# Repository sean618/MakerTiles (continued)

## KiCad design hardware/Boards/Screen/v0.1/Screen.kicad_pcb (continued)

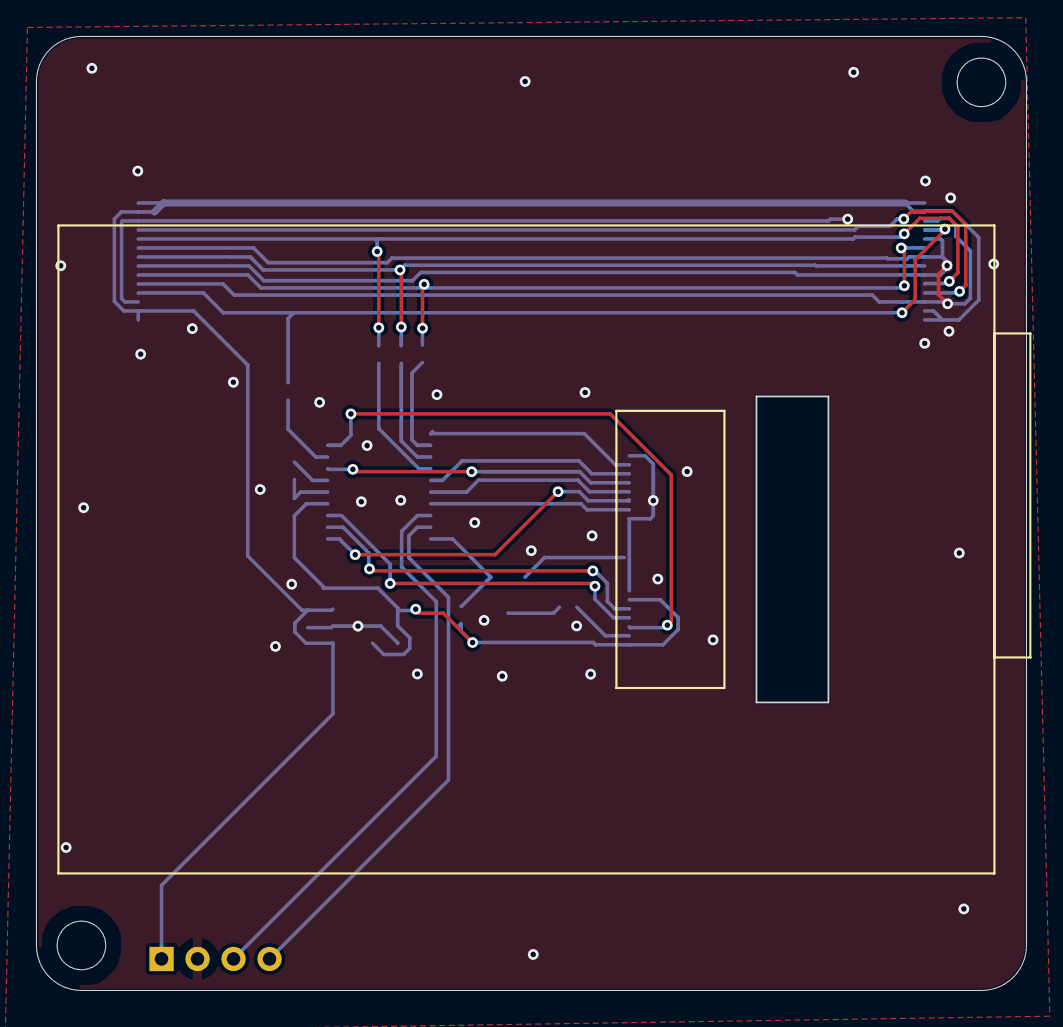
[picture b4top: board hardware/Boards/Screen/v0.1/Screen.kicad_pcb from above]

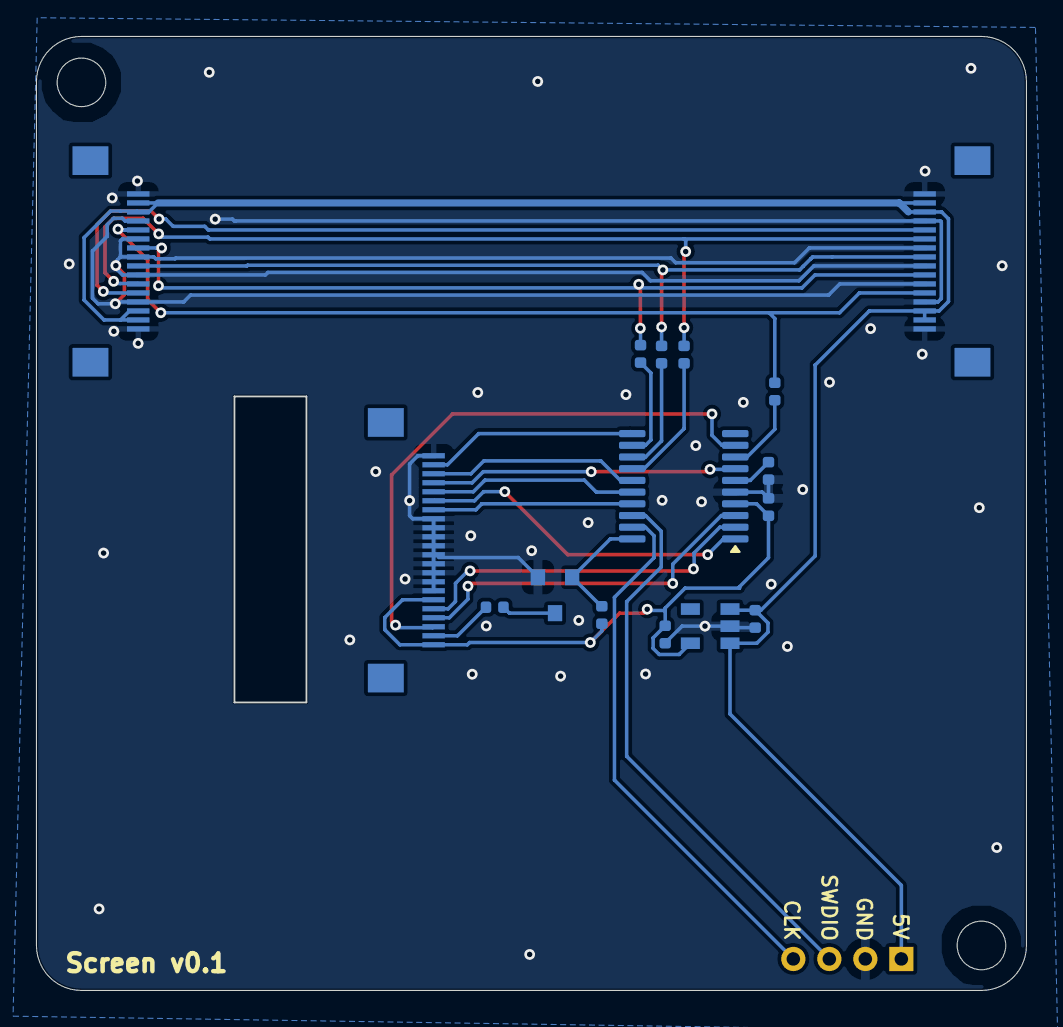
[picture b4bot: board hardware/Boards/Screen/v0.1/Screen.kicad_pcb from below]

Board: 2 copper layers, 55.0 x 53.0 mm, 21 parts (16 on the bottom side), 27 nets.

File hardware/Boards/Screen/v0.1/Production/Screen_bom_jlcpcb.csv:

Comment,Designator,Footprint,LCSC Part Number
4.7uF,"C9,C8,C2",C_0402_1005Metric,C23733
FFC_connector_16p_hinge_lock,"J1,J2",FFC_connector_16p_hinge_lock,C262665
FFC_connector_22p_dual_sided,J3,FFC_connector_22p_hinge_lock,C557729
ME6211C33M5G-N,U2,SOT-23-5,C81233
75R,"R2,R3,R4,R1",R_0402_1005Metric,C25133
STM32G030F6P6,U3,TSSOP-20_4.4x6.5mm_P0.65mm,C529330
N_MOSFET,Q2,SOT-23,C8545
0.1uF,C1,C_0402_1005Metric,C1525
10R,R5,R_0402_1005Metric,C25077
10K,R7,R_0402_1005Metric,C25744

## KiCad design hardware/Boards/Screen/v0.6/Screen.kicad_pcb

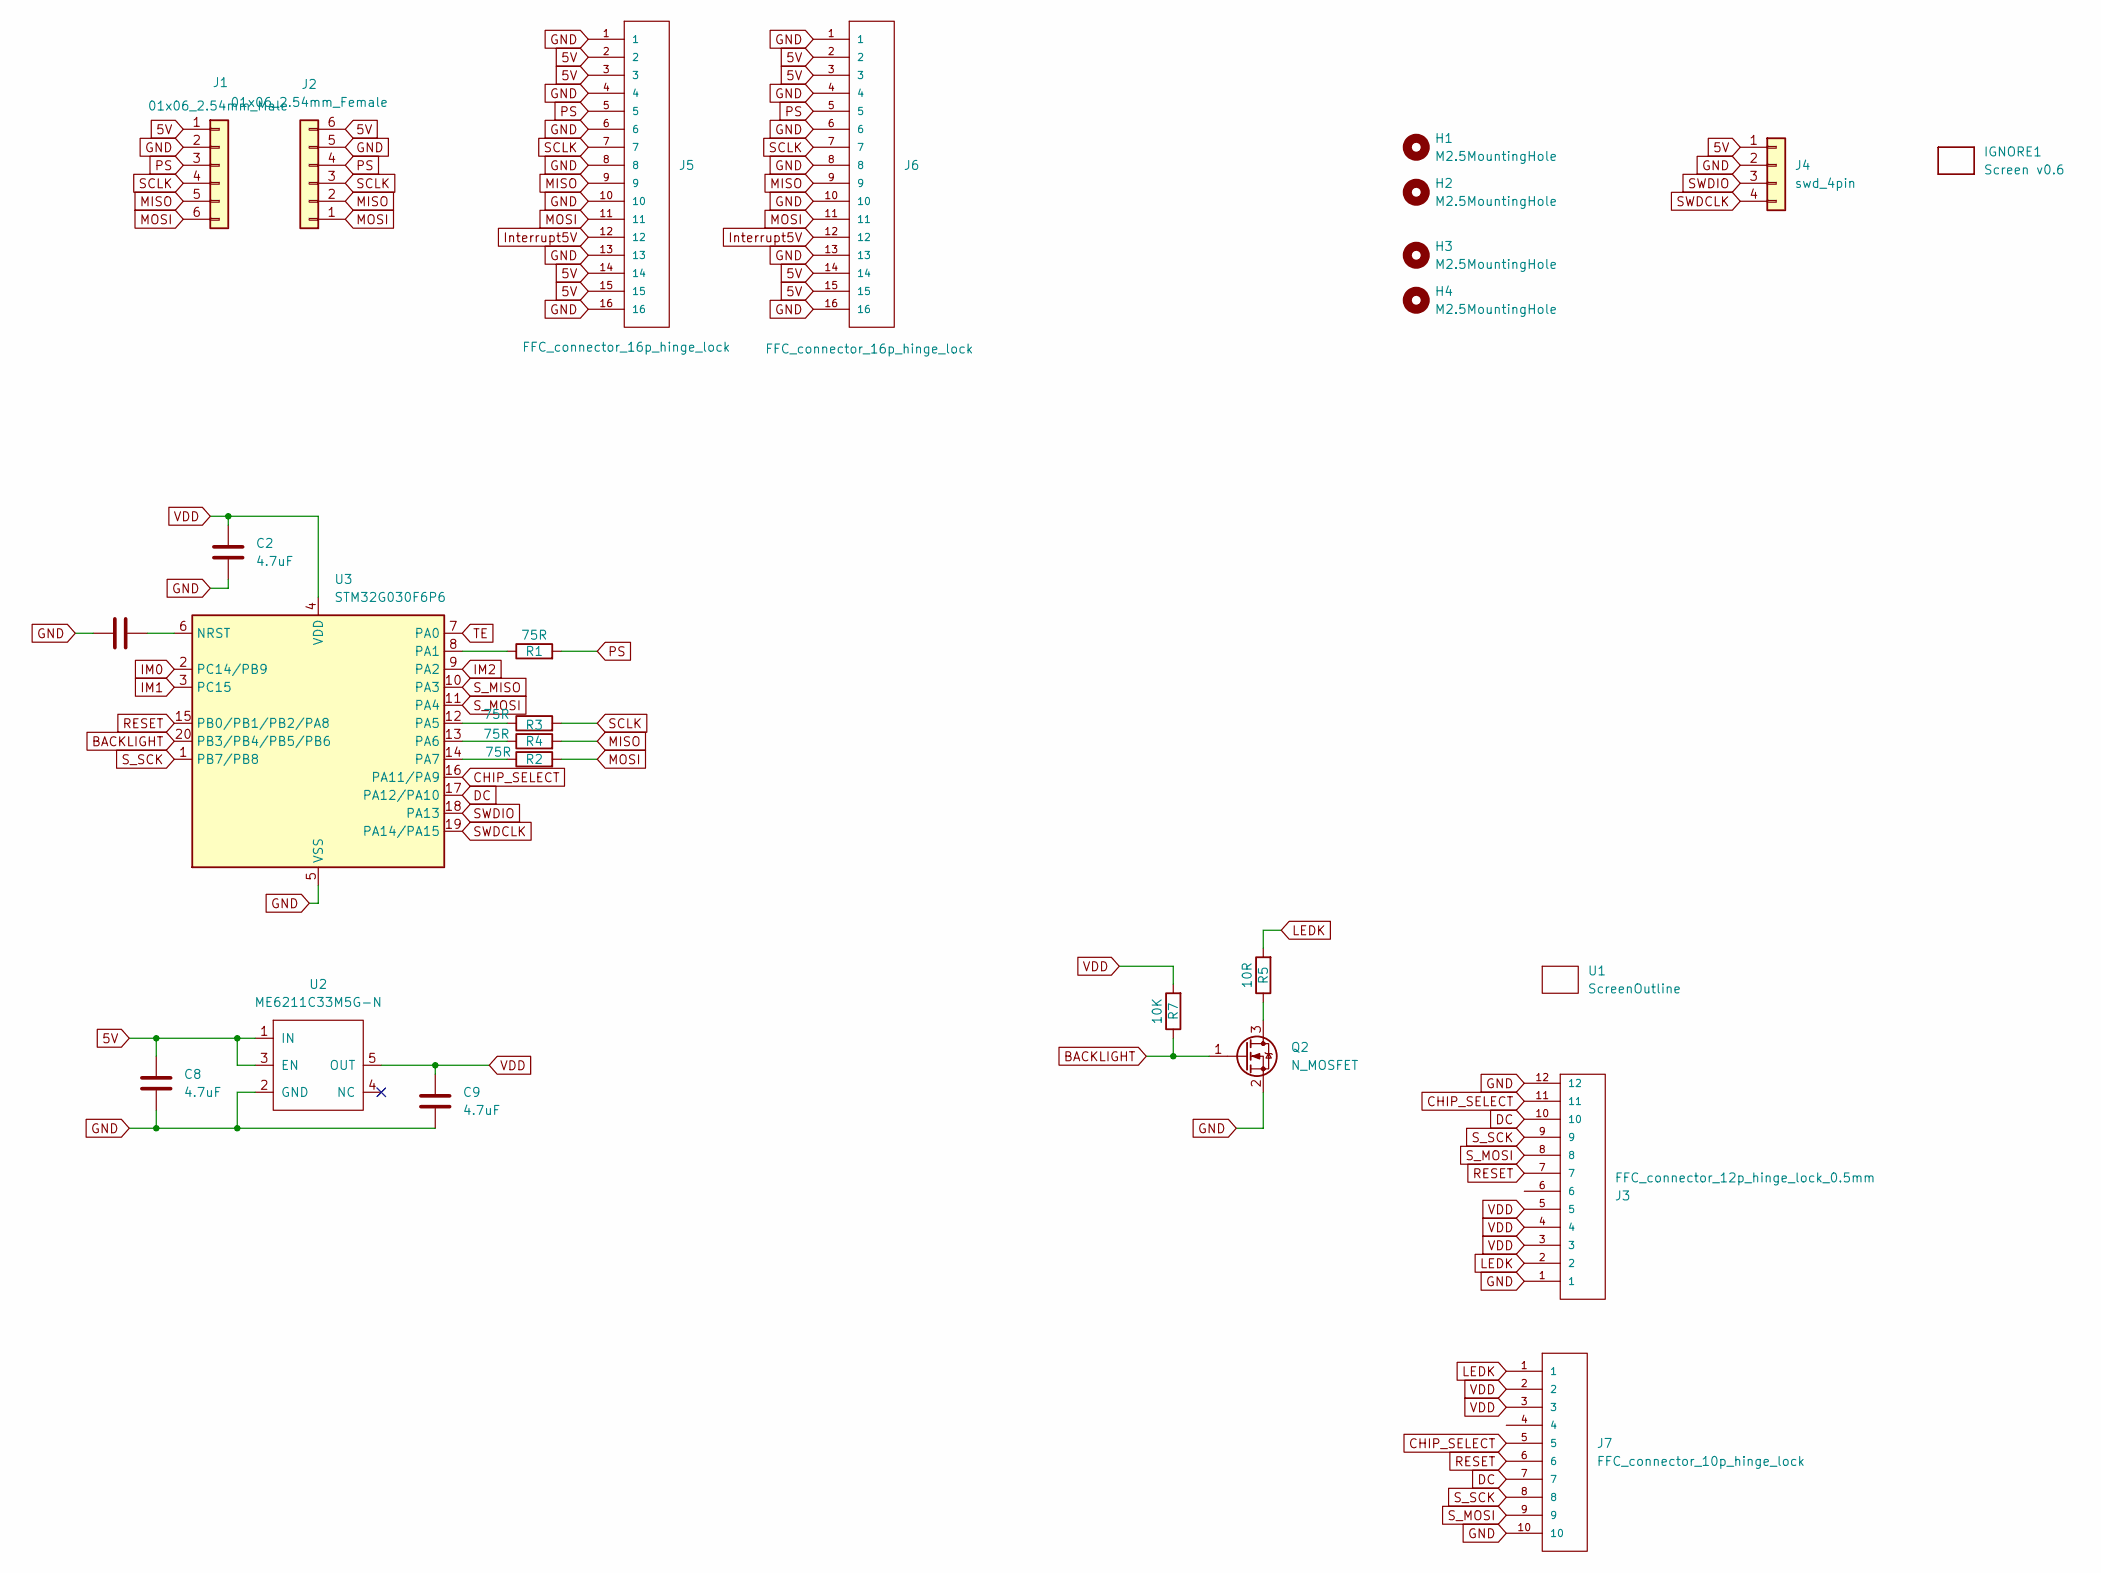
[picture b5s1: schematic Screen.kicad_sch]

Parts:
C1: 0.1uF; C_0402_1005Metric
C2, C8, C9: 4.7uF; C_0402_1005Metric
H1, H2, H3, H4: M2.5MountingHole; MountingHole_2.7mm_M2.5_ISO7380
IGNORE1: Screen v0.6; BoardText
J1: 01x06_2.54mm_Male
J2: 01x06_2.54mm_Female
J3: FFC_connector_12p_hinge_lock_0.5mm
J4: swd_4pin; swd_header
J5, J6: FFC_connector_16p_hinge_lock
J7: FFC_connector_10p_hinge_lock
Q2: N_MOSFET; SOT-23
R1, R2, R3, R4: 75R; R_0402_1005Metric
R5: 10R; R_0402_1005Metric
R7: 10K; R_0402_1005Metric
U1: ScreenOutline; 2InchScreen
U2: ME6211C33M5G-N; SOT-23-5
U3: STM32G030F6P6; TSSOP-20_4.4x6.5mm_P0.65mm

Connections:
5V: C8.1, J1.1, J2.6, J4.1, J5.2, J5.3, J5.14, J5.15, J6.2, J6.3, J6.14, J6.15, U2.1 (IN), U2.3 (EN)
BACKLIGHT: Q2.1 (G), R7.1, U3.20 (PB3/PB4/PB5/PB6)
CHIP_SELECT: J3.11, J7.5, U3.16 (PA11/PA9)
DC: J3.10, J7.7, U3.17 (PA12/PA10)
GND: C1.2, C2.2, C8.2, C9.2, J1.2, J2.5, J3.1, J3.12, J4.2, J5.1, J5.4, J5.6, J5.8, J5.10, J5.13, J5.16, J6.1, J6.4, J6.6, J6.8, J6.10, J6.13, J6.16, J7.10, Q2.2 (S), U2.2 (GND), U3.5 (VSS)
IM0: U3.2 (PC14/PB9)
IM1: U3.3 (PC15)
IM2: U3.9 (PA2)
Interrupt5V: J5.12, J6.12
LEDK: J3.2, J7.1, R5.2
MISO: J1.5, J2.2, J5.9, J6.9, R4.2
MOSI: J1.6, J2.1, J5.11, J6.11, R2.2
unnamed: Q2.3 (D), R5.1
unnamed: C1.1, U3.6 (NRST)
unnamed: R1.1, U3.8 (PA1)
unnamed: R3.1, U3.12 (PA5)
unnamed: R4.1, U3.13 (PA6)
unnamed: R2.1, U3.14 (PA7)
PS: J1.3, J2.4, J5.5, J6.5, R1.2
RESET: J3.7, J7.6, U3.15 (PB0/PB1/PB2/PA8)
SCLK: J1.4, J2.3, J5.7, J6.7, R3.2
SWDCLK: J4.4, U3.19 (PA14/PA15)
SWDIO: J4.3, U3.18 (PA13)
S_MISO: U3.10 (PA3)
S_MOSI: J3.8, J7.9, U3.11 (PA4)
S_SCK: J3.9, J7.8, U3.1 (PB7/PB8)
TE: U3.7 (PA0)
VDD: C2.1, C9.1, J3.3, J3.4, J3.5, J7.2, J7.3, R7.2, U2.5 (OUT), U3.4 (VDD)

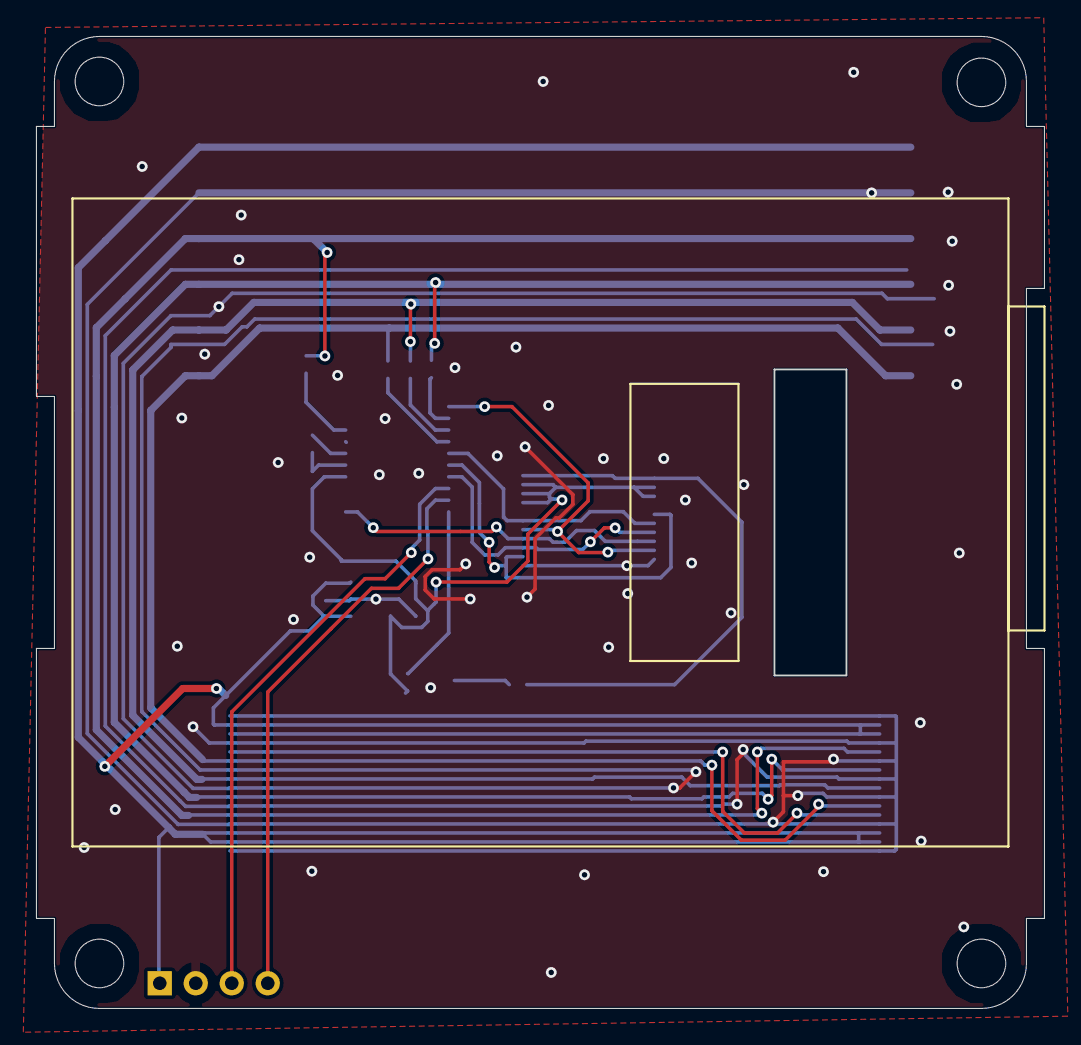
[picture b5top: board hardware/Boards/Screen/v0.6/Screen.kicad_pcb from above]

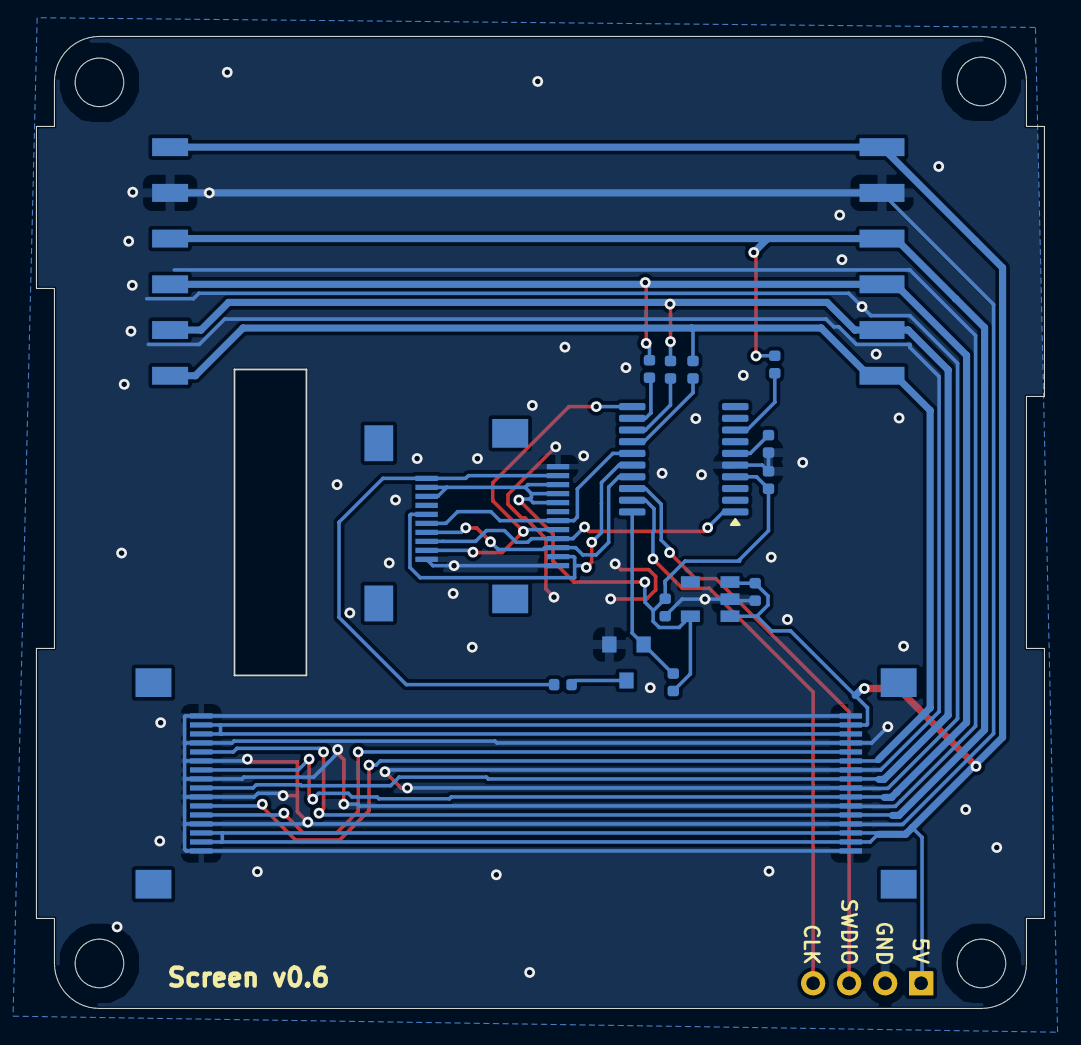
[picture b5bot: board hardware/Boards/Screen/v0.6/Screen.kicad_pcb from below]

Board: 2 copper layers, 56.0 x 54.0 mm, 26 parts (19 on the bottom side), 23 nets.

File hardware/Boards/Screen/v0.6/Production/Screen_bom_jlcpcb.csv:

Comment,Designator,Footprint,LCSC Part Number
4.7uF,"C9,C8,C2",C_0402_1005Metric,C23733
FFC_connector_12p_hinge_lock_0.5mm,J3,FFC_connector_12p_hinge_lock_0.5mm,C262661
FFC_connector_16p_hinge_lock,"J5,J6",FFC_connector_16p_hinge_lock,C262665
ME6211C33M5G-N,U2,SOT-23-5,C81233
75R,"R2,R3,R4,R1",R_0402_1005Metric,C25133
STM32G030F6P6,U3,TSSOP-20_4.4x6.5mm_P0.65mm,C529330
N_MOSFET,Q2,SOT-23,C8545
0.1uF,C1,C_0402_1005Metric,C1525
FFC_connector_10p_hinge_lock,J7,FFC_connector_10p_hinge_lock,C262659
01x06_2.54mm_Female,J2,01x06_2.54mm_Female,C5142239
10R,R5,R_0402_1005Metric,C25077
01x06_2.54mm_Male,J1,01x06_2.54mm_Male,C5242199
10K,R7,R_0402_1005Metric,C25744

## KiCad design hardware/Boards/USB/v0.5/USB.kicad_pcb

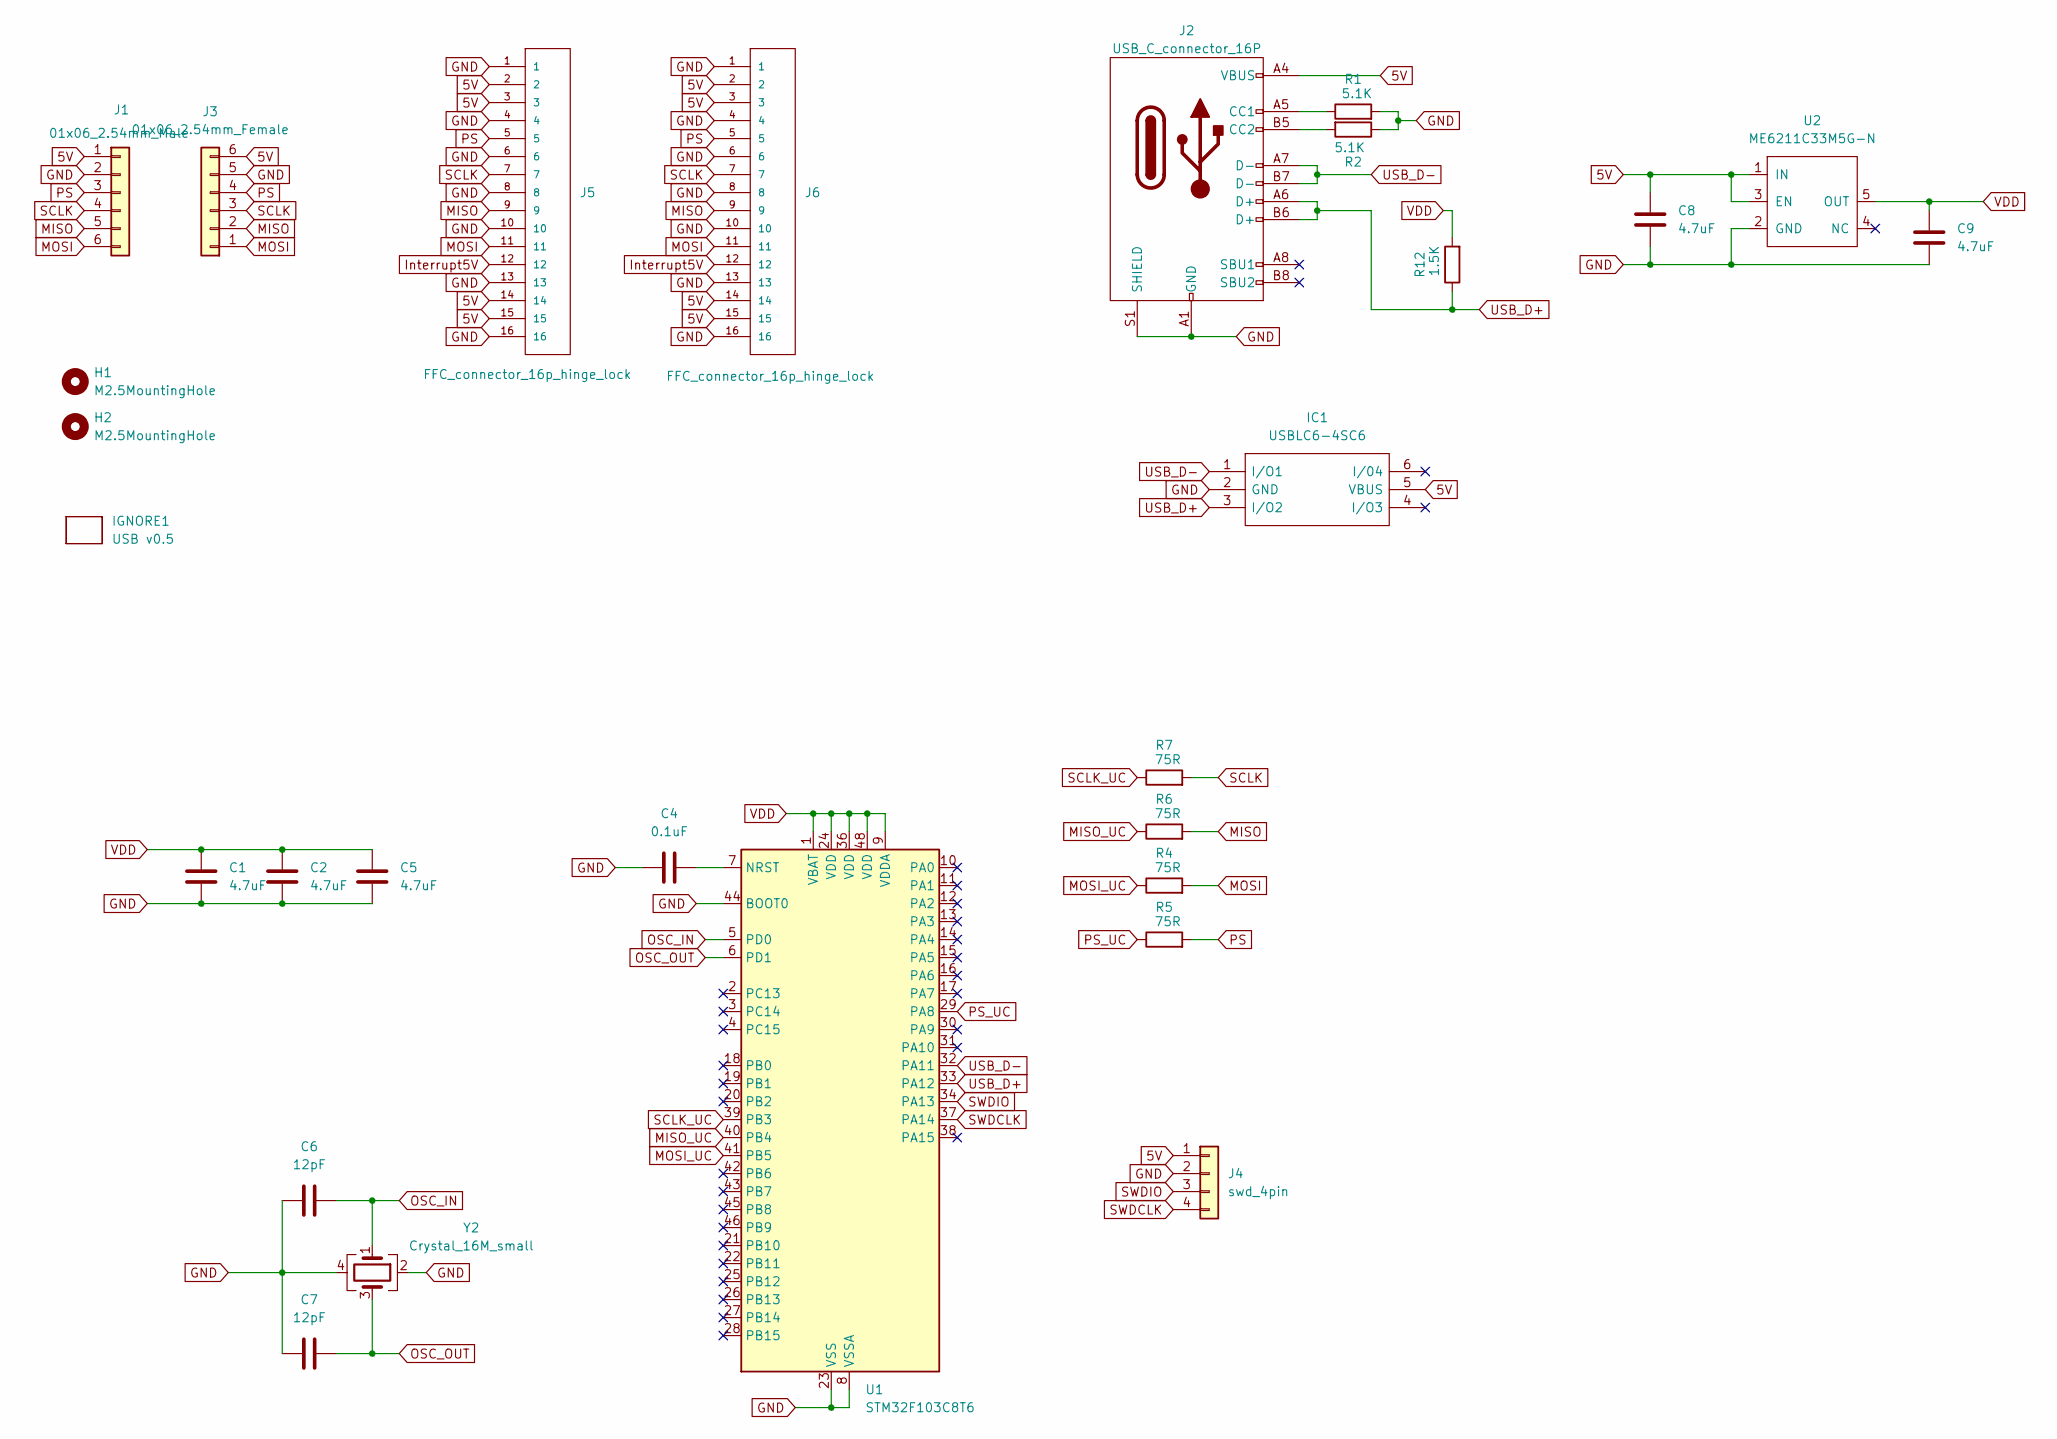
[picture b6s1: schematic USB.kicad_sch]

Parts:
C1, C2, C5, C8, C9: 4.7uF; C_0402_1005Metric
C4: 0.1uF; C_0402_1005Metric
C6, C7: 12pF; C_0402_1005Metric
H1, H2: M2.5MountingHole; MountingHole_2.7mm_M2.5_ISO7380
IC1: USBLC6-4SC6; SOT-23-6; Manufacturer_Part_Number USBLC6-2P6
IGNORE1: USB v0.5; BoardText
J1: 01x06_2.54mm_Male
J2: USB_C_connector_16P; USB_C_Receptacle_16P
J3: 01x06_2.54mm_Female
J4: swd_4pin; swd_header
J5, J6: FFC_connector_16p_hinge_lock
R1, R2: 5.1K; R_0402_1005Metric
R4, R5, R6, R7: 75R; R_0402_1005Metric
R12: 1.5K; R_0402_1005Metric
U1: STM32F103C8T6; LQFP-48_7x7mm_P0.5mm
U2: ME6211C33M5G-N; SOT-23-5
Y2: Crystal_16M_small; Crystal_SMD_2016-4Pin_2.0x1.6mm

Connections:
5V: C8.1, IC1.5 (VBUS), J1.1, J2.A4 (VBUS), J2.A9 (VBUS), J2.B4 (VBUS), J2.B9 (VBUS), J3.6, J4.1, J5.2, J5.3, J5.14, J5.15, J6.2, J6.3, J6.14, J6.15, U2.1 (IN), U2.3 (EN)
GND: C1.2, C2.2, C4.1, C5.2, C6.1, C7.1, C8.2, C9.2, IC1.2 (GND), J1.2, J2.A1 (GND), J2.A12 (GND), J2.B1 (GND), J2.B12 (GND), J2.S1 (SHIELD), J3.5, J4.2, J5.1, J5.4, J5.6, J5.8, J5.10, J5.13, J5.16, J6.1, J6.4, J6.6, J6.8, J6.10, J6.13, J6.16, R1.2, R2.1, U1.8 (VSSA), U1.23 (VSS), U1.35 (VSS), U1.44 (BOOT0), U1.47 (VSS), U2.2 (GND), Y2.2 (GND), Y2.4 (GND)
Interrupt5V: J5.12, J6.12
MISO: J1.5, J3.2, J5.9, J6.9, R6.2
MISO_UC: R6.1, U1.40 (PB4)
MOSI: J1.6, J3.1, J5.11, J6.11, R4.2
MOSI_UC: R4.1, U1.41 (PB5)
unnamed: J2.A5 (CC1), R1.1
unnamed: J2.B5 (CC2), R2.2
unnamed: C4.2, U1.7 (NRST)
OSC_IN: C6.2, U1.5 (PD0), Y2.1
OSC_OUT: C7.2, U1.6 (PD1), Y2.3
PS: J1.3, J3.4, J5.5, J6.5, R5.2
PS_UC: R5.1, U1.29 (PA8)
SCLK: J1.4, J3.3, J5.7, J6.7, R7.2
SCLK_UC: R7.1, U1.39 (PB3)
SWDCLK: J4.4, U1.37 (PA14)
SWDIO: J4.3, U1.34 (PA13)
USB_D+: IC1.3 (I/O2), J2.A6 (D+), J2.B6 (D+), R12.1, U1.33 (PA12)
USB_D-: IC1.1 (I/O1), J2.A7 (D-), J2.B7 (D-), U1.32 (PA11)
VDD: C1.1, C2.1, C5.1, C9.1, R12.2, U1.1 (VBAT), U1.9 (VDDA), U1.24 (VDD), U1.36 (VDD), U1.48 (VDD), U2.5 (OUT)

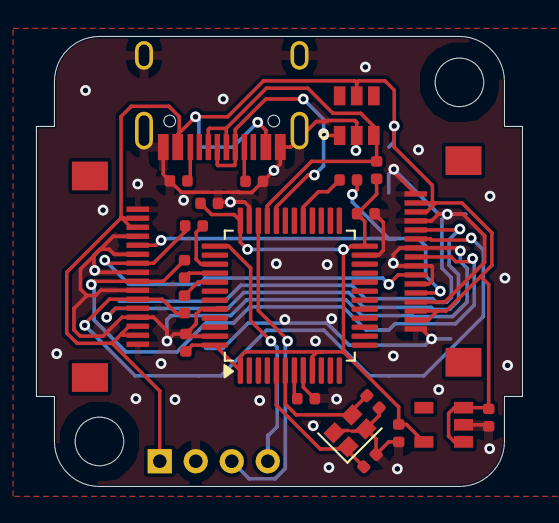
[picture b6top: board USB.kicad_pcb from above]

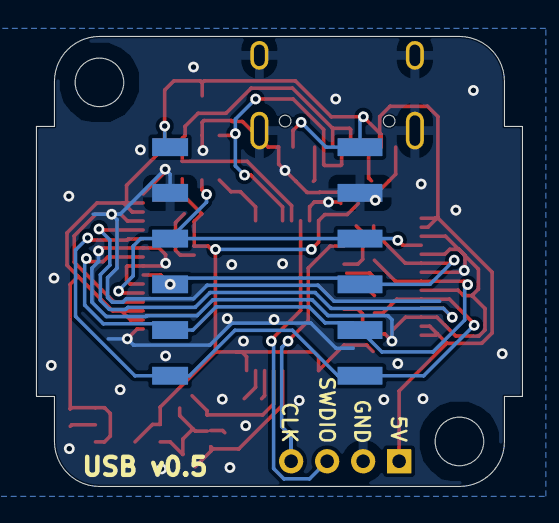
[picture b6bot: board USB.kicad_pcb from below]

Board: 4 copper layers, 27.0 x 25.0 mm, 28 parts (2 on the bottom side), 21 nets.

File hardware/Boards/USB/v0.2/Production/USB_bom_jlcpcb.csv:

Comment,Designator,Footprint,LCSC Part Number
1.5K,R12,R_0402_1005Metric,C25867
4.7uF,"C9,C2,C8,C3,C5,C1",C_0402_1005Metric,C23733
FFC_connector_16p_hinge_lock,"J1,J3",FFC_connector_16p_hinge_lock,C262665
12pF,"C6,C7",C_0402_1005Metric,C1547
STM32F103C8T6,U1,LQFP-48_7x7mm_P0.5mm,C2969777
100R,"R7,R4,R5,R6",R_0402_1005Metric,C25076
ME6211C33M5G-N,U2,SOT-23-5,C82942
5.1K,"R2,R1",R_0402_1005Metric,C25905
USBLC6-4SC6,IC1,SOT-23-6,C558419
0.1uF,C4,C_0402_1005Metric,C1525
Crystal_16M,Y1,Crystal_SMD_3225-4Pin_3.2x2.5mm,C13738
USB_C_connector_16P,J2,USB_C_Receptacle_16P,C319148

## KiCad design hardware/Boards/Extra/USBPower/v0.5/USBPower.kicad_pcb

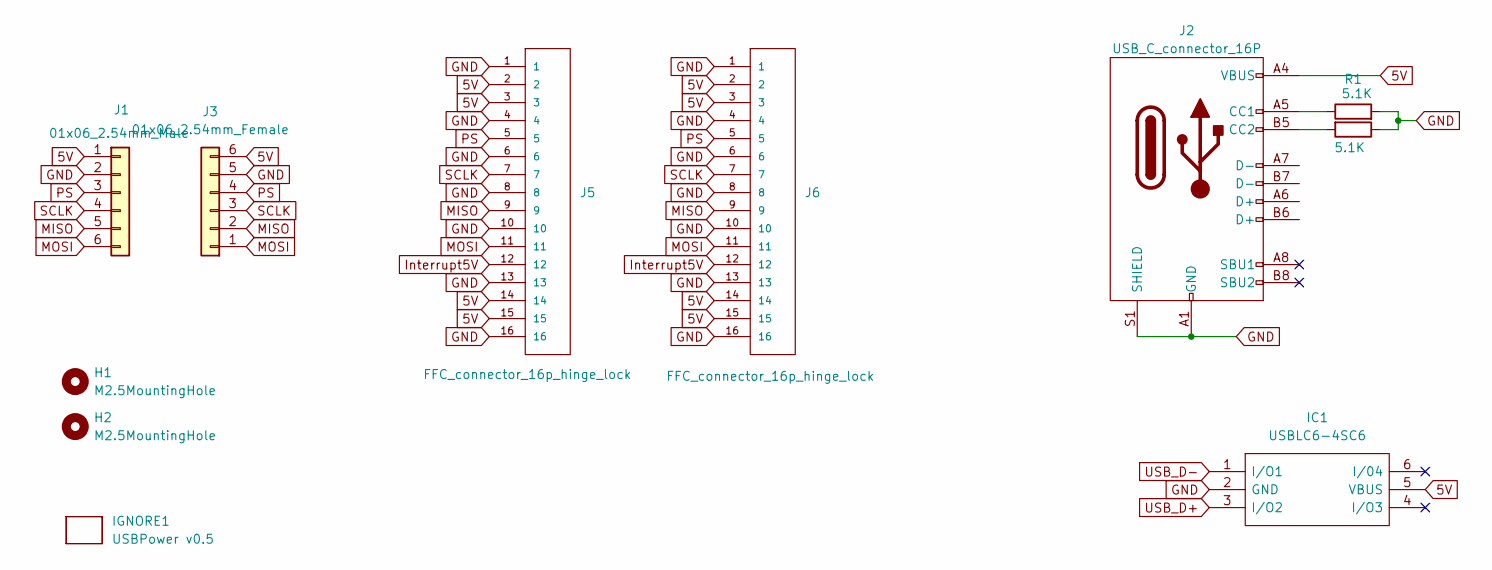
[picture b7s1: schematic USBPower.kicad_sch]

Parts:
H1, H2: M2.5MountingHole; MountingHole_2.7mm_M2.5_ISO7380
IC1: USBLC6-4SC6; SOT-23-6; Manufacturer_Part_Number USBLC6-2P6
IGNORE1: USBPower v0.5; BoardText
J1: 01x06_2.54mm_Male
J2: USB_C_connector_16P; USB_C_Receptacle_16P
J3: 01x06_2.54mm_Female
J5, J6: FFC_connector_16p_hinge_lock
R1, R2: 5.1K; R_0402_1005Metric

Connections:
5V: IC1.5 (VBUS), J1.1, J2.A4 (VBUS), J2.A9 (VBUS), J2.B4 (VBUS), J2.B9 (VBUS), J3.6, J5.2, J5.3, J5.14, J5.15, J6.2, J6.3, J6.14, J6.15
GND: IC1.2 (GND), J1.2, J2.A1 (GND), J2.A12 (GND), J2.B1 (GND), J2.B12 (GND), J2.S1 (SHIELD), J3.5, J5.1, J5.4, J5.6, J5.8, J5.10, J5.13, J5.16, J6.1, J6.4, J6.6, J6.8, J6.10, J6.13, J6.16, R1.2, R2.1
Interrupt5V: J5.12, J6.12
MISO: J1.5, J3.2, J5.9, J6.9
MOSI: J1.6, J3.1, J5.11, J6.11
unnamed: J2.A5 (CC1), R1.1
unnamed: J2.B5 (CC2), R2.2
PS: J1.3, J3.4, J5.5, J6.5
SCLK: J1.4, J3.3, J5.7, J6.7
USB_D+: IC1.3 (I/O2)
USB_D-: IC1.1 (I/O1)

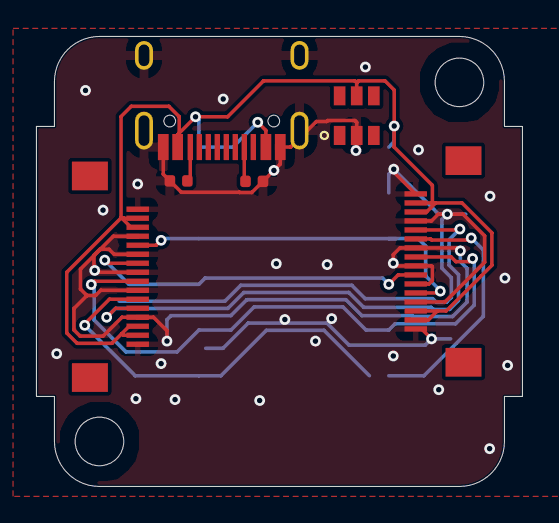
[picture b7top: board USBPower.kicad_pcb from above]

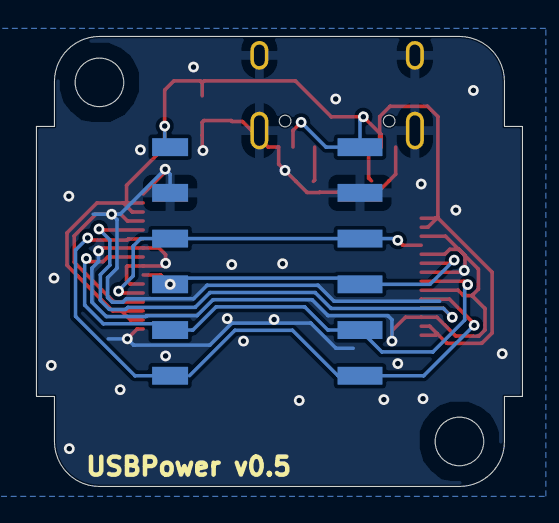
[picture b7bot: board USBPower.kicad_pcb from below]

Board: 4 copper layers, 27.0 x 25.0 mm, 11 parts (2 on the bottom side), 9 nets.

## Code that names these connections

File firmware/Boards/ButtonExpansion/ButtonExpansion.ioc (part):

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Mcu.Name=STM32G030K(6-8)Tx
Mcu.Package=LQFP32
Mcu.UserName=STM32G030K6Tx
PA0.Mode=Full_Duplex_Slave
PA0.Signal=SPI2_SCK
PA1.GPIOParameters=GPIO_PuPd
PA1.GPIO_PuPd=GPIO_NOPULL
PA1.Signal=GPXTI1
PA10.Mode=Full_Duplex_Slave
PA10.Signal=SPI2_MOSI
PA11\ [PA9].GPIOParameters=GPIO_PuPd
PA11\ [PA9].GPIO_PuPd=GPIO_PULLUP
PA11\ [PA9].Signal=GPIO_Input
PA12\ [PA10].GPIOParameters=GPIO_PuPd
PA12\ [PA10].GPIO_PuPd=GPIO_PULLUP
PA12\ [PA10].Signal=GPIO_Input
PA13.Mode=Serial_Wire
PA13.Signal=SYS_SWDIO
PA14-BOOT0.Mode=Serial_Wire
PA14-BOOT0.Signal=SYS_SWCLK
PA15.GPIOParameters=GPIO_PuPd
PA15.GPIO_PuPd=GPIO_PULLUP
PA15.Signal=GPIO_Input
PA2.GPIOParameters=GPIO_PuPd
PA2.GPIO_PuPd=GPIO_PULLUP
PA2.Signal=GPIO_Input
PA3.GPIOParameters=GPIO_PuPd
PA3.GPIO_PuPd=GPIO_PULLUP
PA3.Signal=GPIO_Input
PA4.GPIOParameters=GPIO_PuPd
PA4.GPIO_PuPd=GPIO_PULLUP
PA4.Signal=GPIO_Input
PA5.GPIOParameters=GPIO_PuPd
PA5.GPIO_PuPd=GPIO_PULLUP
PA5.Signal=GPIO_Input
PA6.GPIOParameters=GPIO_PuPd
PA6.GPIO_PuPd=GPIO_PULLUP
PA6.Signal=GPIO_Input
PA7.GPIOParameters=GPIO_PuPd
PA7.GPIO_PuPd=GPIO_PULLUP
PA7.Signal=GPIO_Input
PA8.GPIOParameters=GPIO_PuPd
PA8.GPIO_PuPd=GPIO_PULLUP
PA8.Signal=GPIO_Input
PA9.Mode=Full_Duplex_Slave
PA9.Signal=SPI2_MISO
PB0.GPIOParameters=GPIO_PuPd
PB0.GPIO_PuPd=GPIO_PULLUP
PB0.Signal=GPIO_Input
PB1.GPIOParameters=GPIO_PuPd
PB1.GPIO_PuPd=GPIO_PULLUP
PB1.Signal=GPIO_Input
PB2.GPIOParameters=GPIO_PuPd
PB2.GPIO_PuPd=GPIO_PULLUP
PB2.Signal=GPIO_Input
PB3.GPIOParameters=GPIO_PuPd
PB3.GPIO_PuPd=GPIO_PULLUP
PB3.Signal=GPIO_Input
PB4.GPIOParameters=GPIO_PuPd
PB4.GPIO_PuPd=GPIO_PULLUP
PB4.Signal=GPIO_Input
PB5.GPIOParameters=GPIO_PuPd
PB5.GPIO_PuPd=GPIO_PULLUP
PB5.Signal=GPIO_Input
PB6.GPIOParameters=GPIO_PuPd
PB6.GPIO_PuPd=GPIO_PULLUP
PB6.Signal=GPIO_Input
PB7.GPIOParameters=GPIO_PuPd
PB7.GPIO_PuPd=GPIO_PULLUP
PB7.Signal=GPIO_Input
PB8.GPIOParameters=GPIO_PuPd
PB8.GPIO_PuPd=GPIO_PULLUP
PB8.Signal=GPIO_Input
PB9.GPIOParameters=GPIO_PuPd
PB9.GPIO_PuPd=GPIO_PULLUP
PB9.Signal=GPIO_Input
PC14-OSC32_IN\ (PC14).GPIOParameters=GPIO_PuPd
PC14-OSC32_IN\ (PC14).GPIO_PuPd=GPIO_PULLUP
PC14-OSC32_IN\ (PC14).Signal=GPIO_Input
PC15-OSC32_OUT\ (PC15).GPIOParameters=GPIO_PuPd
PC15-OSC32_OUT\ (PC15).GPIO_PuPd=GPIO_PULLUP
PC15-OSC32_OUT\ (PC15).Signal=GPIO_Input
RCC.HSE_VALUE=8000000
RCC.SYSCLKFreq_VALUE=48000000
RCC.SYSCLKSource=RCC_SYSCLKSOURCE_PLLCLK
board=custom

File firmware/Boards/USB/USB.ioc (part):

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Mcu.Name=STM32F103C(8-B)Tx
Mcu.Package=LQFP48
Mcu.UserName=STM32F103C8Tx
PA11.Mode=Device
PA11.Signal=USB_DM
PA12.Mode=Device
PA12.Signal=USB_DP
PA13.Mode=Serial_Wire
PA13.Signal=SYS_JTMS-SWDIO
PA14.Mode=Serial_Wire
PA14.Signal=SYS_JTCK-SWCLK
PA8.Signal=GPIO_Output
PB3.Mode=Full_Duplex_Master
PB3.Signal=SPI1_SCK
PB4.GPIOParameters=GPIO_PuPd
PB4.GPIO_PuPd=GPIO_PULLUP
PB4.Mode=Full_Duplex_Master
PB4.Signal=SPI1_MISO
PB5.Mode=Full_Duplex_Master
PB5.Signal=SPI1_MOSI
PD0-OSC_IN.Mode=HSE-External-Oscillator
PD0-OSC_IN.Signal=RCC_OSC_IN
PD1-OSC_OUT.Mode=HSE-External-Oscillator
PD1-OSC_OUT.Signal=RCC_OSC_OUT
RCC.HSEDivPLL=RCC_HSE_PREDIV_DIV2
RCC.HSE_VALUE=16000000
RCC.SYSCLKFreq_VALUE=72000000
RCC.SYSCLKSource=RCC_SYSCLKSOURCE_PLLCLK
board=custom
